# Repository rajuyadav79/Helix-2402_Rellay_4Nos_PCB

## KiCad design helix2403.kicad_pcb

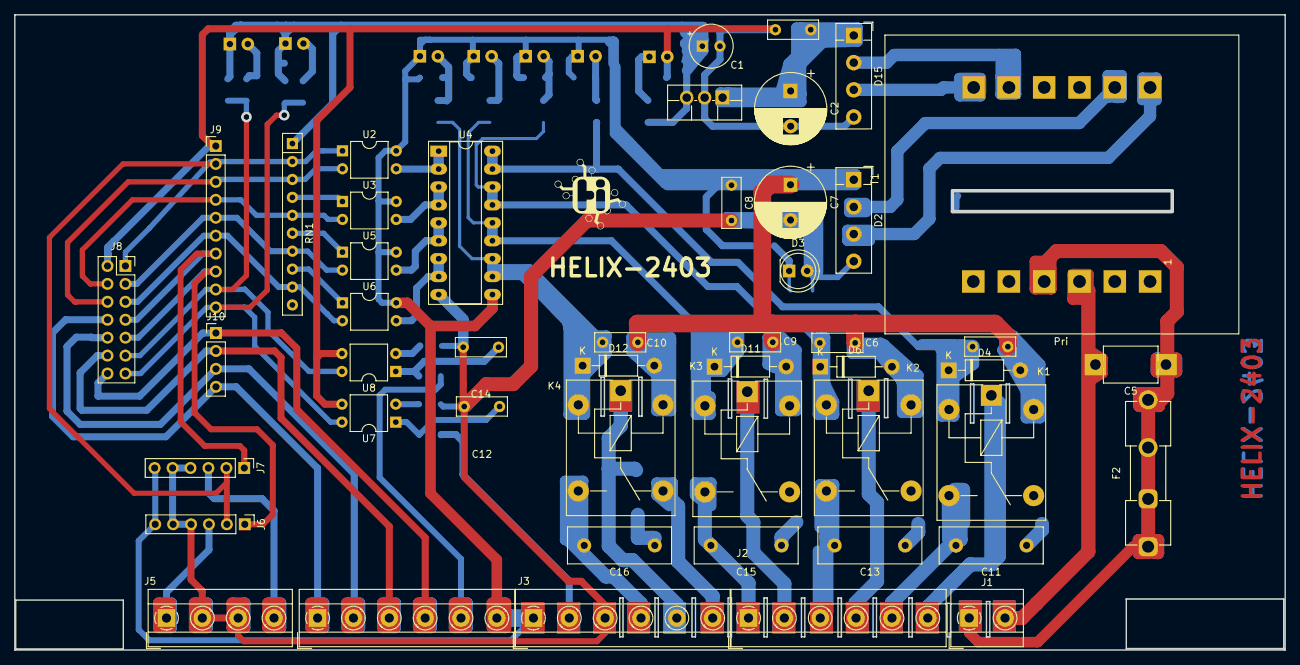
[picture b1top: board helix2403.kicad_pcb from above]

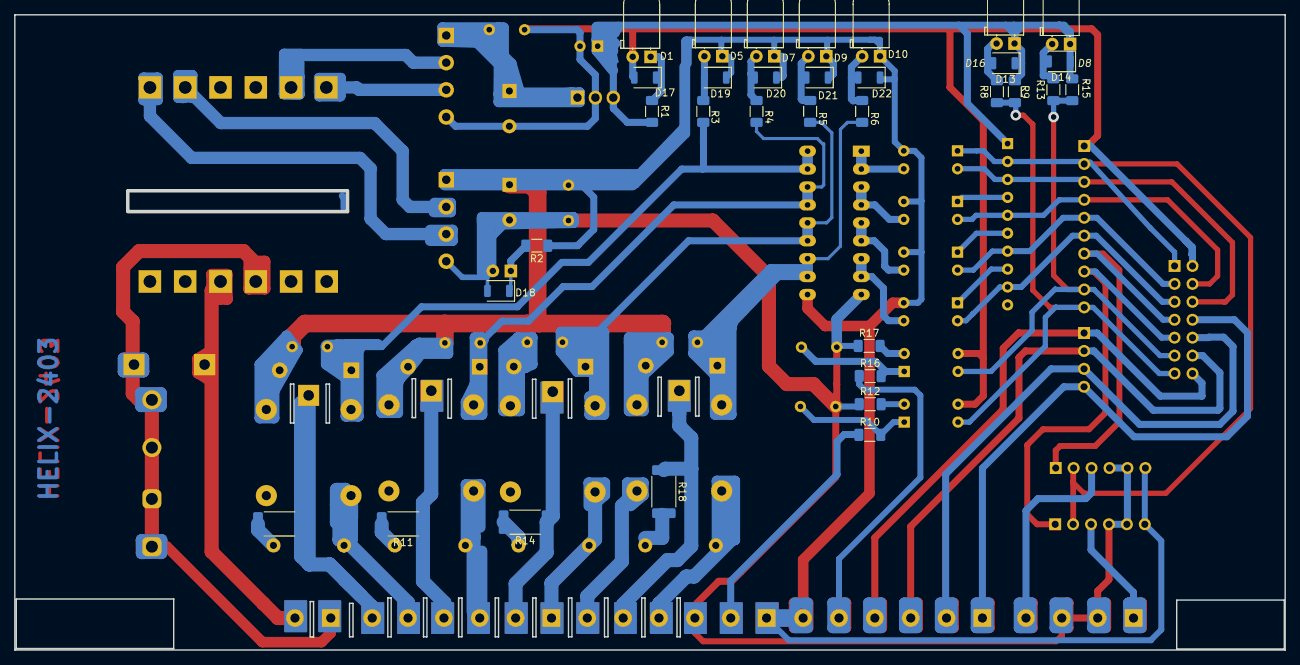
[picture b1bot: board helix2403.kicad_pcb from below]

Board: 2 copper layers, 179.7 x 89.7 mm, 81 parts (33 on the bottom side), 63 nets.

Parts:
C1: C_1000mg/16v; CP_Radial_Tantal_D6.0mm_P2.50mm
C2, C7: C_1000mg/16v; CP_Radial_D10.0mm_P5.00mm
C3, C8: C104; C_Disc_D7.0mm_W2.5mm_P5.00mm
C4, C6, C9, C10, C12, C14: C_0.1/100V_BOX; C_Disc_D7.0mm_W2.5mm_P5.00mm
C5: 47NK630V_BOXTYPE; C_Disc_D7.5mm_W5.0mm_P10.00mm
C11, C13, C15, C16: 47NK630V_BOXTYPE; C_Disc_D14.5mm_W5.0mm_P10.00mm
D1, D5, D7, D9, D10, D13, D14: LED; LED_D5.0mm_Horizontal_O1.27mm_Z3.0mm
D2, D15: KBU4A; Diode_Bridge_Vishay_KBPM
D3: LED; LED_D5.0mm
D4, D6, D11, D12: 1N4007; D_DO-41_SOD81_P10.16mm_Horizontal
D8, D16, D17, D18, D19, D20, D21, D22: LED; LED_1206_3216Metric_ReverseMount_Hole1.8x2.4mm
F2: Fuse_Small; Fuseholder_Clip-5x20mm_Eaton_1A5601-01_Inline_P20.80x6.76mm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
J1: Conn_01x02_Pin; TerminalBlock_MetzConnect_Type101_RT01602HBWC_1x02_P5.08mm_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
J2, J3, J4: Conn_01x06; TerminalBlock_MetzConnect_Type101_RT01606HBWC_1x06_P5.08mm_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
J5: Conn_01x04_Pin; TerminalBlock_MetzConnect_Type101_RT01604HBWC_1x04_P5.08mm_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
J6, J7: Conn_01x06; PinHeader_1x06_P2.54mm_Vertical
J8: Conn_02x07_Odd_Even; PinSocket_2x07_P2.54mm_Vertical
J9: Conn_01x10; PinHeader_1x10_P2.54mm_Vertical
J10: Conn_01x04_Pin; PinHeader_1x04_P2.54mm_Vertical
K1, K2, K3, K4: FINDER-36.11; Relay_SPDT_Finder_36.11
R1, R2, R9, R15: 10K; R_1206_3216Metric_Pad1.30x1.75mm_HandSolder
R3, R4, R5, R6, R8, R13: 3k3; R_1206_3216Metric_Pad1.30x1.75mm_HandSolder
R7, R11, R14, R18: 100e / 1w; R_2512_6332Metric_Pad1.40x3.35mm_HandSolder
R10, R12, R16, R17: 2k2; R_1206_3216Metric_Pad1.30x1.75mm_HandSolder
RN1: R_Network09_US; R_Array_SIP10
T1: Transformer_1P_2S; Transformer_CHK_EI48-8VA_2xSec
U1: LM7805_TO220; TO-220F-3_Vertical
U2, U3, U5, U6, U7, U8: PC817; DIP-4_W7.62mm
U4: ULN2803A; DIP-18_W7.62mm_Socket_LongPads

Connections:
/0-10 output1: J5.1, J6.3
/0-10 output2: J5.4, J7.3
/BLACK: J4.2, J8.10, J10.3
/C1: J2.6, K1.11, R7.1
/C2: J2.4, K2.11, R11.1
/C3: J2.2, K3.11, R14.1
/C4: J3.5, K4.11, R18.1
/GREEN: J4.4, J8.14, J10.1
/Input1: J4.5, R16.1
/Line: C5.2, J1.2, T1.3 (AA)
/NC4: J3.6, K4.12
/NO1: C11.2, J2.5, K1.14
/NO2: C13.2, J2.3, K2.14
/NO3: C15.2, J2.1, K3.14
/NO4: C16.2, J3.4, K4.14
/Nutral: C5.1, F2.1, F2.2, J1.1, T1.4 (AB)
/RED: J4.1, J8.8, J10.4
/RL1: C4.2, D4.1 (K), K1.A1, R3.1, U4.17 (O2), U4.18 (O1)
/RL2: C6.2, D6.1 (K), K2.A1, R4.1, U4.15 (O4), U4.16 (O3)
/RL3: C9.2, D11.1 (K), K3.A1, R5.1, U4.13 (O6), U4.14 (O5)
/RL4: C10.2, D12.1 (K), K4.A1, R6.1, U4.11 (O8), U4.12 (O7)
/VCC1 5V: C1.1, D8.1 (K), D13.1 (K), D14.1 (K), D16.1 (K), J6.2, J7.2, J8.1, J9.2, R1.1, R9.2, R15.2, RN1.1 (common), U1.3 (VO)
/VCC2 12V: C4.1, C6.1, C7.1, C8.1, C9.1, C10.1, D2.1 (+), D4.2 (A), D5.1 (K), D6.2 (A), D7.1 (K), D9.1 (K), D10.1 (K), D11.2 (A), D12.2 (A), D19.1 (K), D20.1 (K), D21.1 (K), D22.1 (K), J3.1, J6.6, J7.6, K1.A2, K2.A2, K3.A2, K4.A2, R2.1, U2.4, U3.4, U4.10 (COM), U5.4, U6.4
/WHITE: J4.3, J8.12, J10.2
/mc1: J8.11, J9.9, R13.1, R15.1, U8.4
/mc2: J8.13, J9.10, R8.1, R9.1, U7.4
/mc3: J8.6, J9.3, RN1.3 (R2), U2.2
/mc4: J8.4, J9.4, RN1.5 (R4), U3.2
/mc5: J8.3, J9.5, RN1.7 (R6), U5.2
/mc6: J8.5, J9.6, RN1.9 (R8), U6.2
/pwm MC7: J6.1, J8.9, J9.8
/pwm MC8: J7.1, J8.7, J9.7
GND1: C1.2, C2.2, C3.2, D1.2 (A), D15.4 (-), D17.2 (A), J8.2, J9.1, U1.2 (GND), U7.3, U8.3
GND2: C7.2, C8.2, C12.2, C14.2, D2.4 (-), D3.2 (A), D18.2 (A), J3.3, J5.2, J5.3, J6.4, J6.5, J7.4, J7.5, R12.1, R17.1, U4.9 (GND)
unnamed: C11.1, R7.2
unnamed: C12.1, R10.2, U7.1
unnamed: C13.1, R11.2
unnamed: C14.1, R16.2, U8.1
unnamed: C15.1, R14.2
unnamed: C16.1, R18.2
unnamed: D1.1 (K), D17.1 (K), R1.2
unnamed: D10.2 (A), D22.2 (A), R6.2
unnamed: D13.2 (A), D16.2 (A), R8.2
unnamed: D8.2 (A), D14.2 (A), R13.2
unnamed: C2.1, C3.1, D15.1 (+), U1.1 (VI)
unnamed: D3.1 (K), D18.1 (K), R2.2
unnamed: D5.2 (A), D19.2 (A), R3.2
unnamed: D7.2 (A), D20.2 (A), R4.2
unnamed: D9.2 (A), D21.2 (A), R5.2
unnamed: R12.2, U7.2
unnamed: R17.2, U8.2
unnamed: RN1.2 (R1), U2.1
unnamed: RN1.4 (R3), U3.1
unnamed: RN1.6 (R5), U5.1
unnamed: RN1.8 (R7), U6.1
unnamed: D15.3, T1.7 (SA)
unnamed: D15.2, T1.8 (SB)
unnamed: D2.3, T1.12 (SC)
unnamed: D2.2, T1.11 (SD)
unnamed: U2.3, U4.1 (I1), U4.2 (I2)
unnamed: U3.3, U4.3 (I3), U4.4 (I4)
unnamed: U4.5 (I5), U4.6 (I6), U5.3
unnamed: U4.7 (I7), U4.8 (I8), U6.3

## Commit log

2024-04-19 int rellay pcb fout relay pth
